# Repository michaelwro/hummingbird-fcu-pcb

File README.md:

# hummingbird-fcu-pcb

PCB files for the Hummingbird FCU quadcopter flight controller. Designed with KiCAD.

**Created By:** Michael Wrona, B.S. Aerospace Engineering

YouTube: [@MicWro Engr](https://www.youtube.com/channel/UCIeZzuXHGm7zqSFvT8xGoIQ)

Blog: [Michael Wrona's Blog](https://mwrona.com/)

**BEFORE USING, MAKE SURE YOU FULLY UNDERSTAND THE SCHEMATIC! USE AT YOUR OWN RISK! I AM NOT RESPONSIBLE FOR ANY DAMAGE TO YOUR ELECTRONICS!**

This is the place I store the KiCAD project files for the Humming Flight Control Unit, a quadcopter flight controller that I developed. Feel free to download it and print it!

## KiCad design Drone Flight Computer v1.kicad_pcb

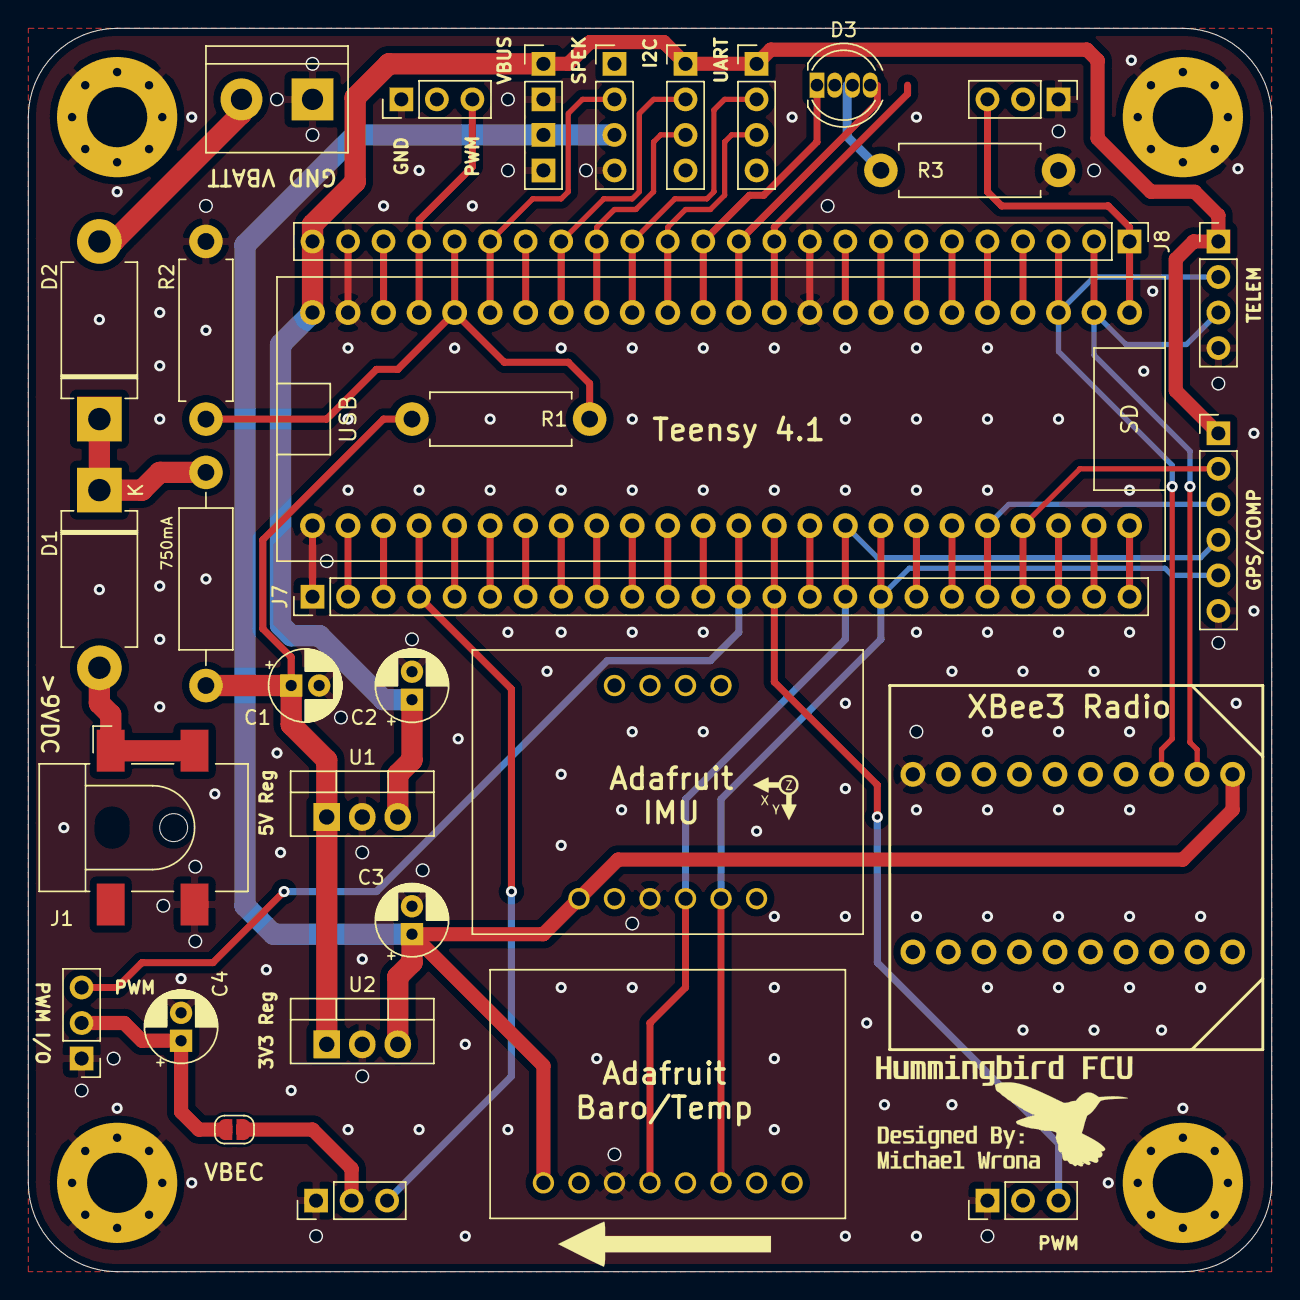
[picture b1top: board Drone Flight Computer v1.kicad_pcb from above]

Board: 2 copper layers, 88.9 x 88.9 mm, 37 parts (0 on the bottom side), 54 nets.

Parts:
C1, C2, C3: 100uF; CP_Radial_D5.0mm_P2.00mm
C4: 10uF; CP_Radial_D5.0mm_P2.00mm
D1, D2: Schottky; D_DO-201AD_P12.70mm_Horizontal
D3: LED_RGBC; LED_D5.0mm-4_RGB
F1: 750mA-1A; R_Axial_DIN0411_L9.9mm_D3.6mm_P15.24mm_Horizontal
H1, H2, H3, H4: MountingHole_Pad; MountingHole_4.3mm_M4_Pad_Via
J1: Jack; BarrelJack_CLIFF_FC681465S_SMT_Horizontal
J2: BATT_VCC; TerminalBlock_bornier-2_P5.08mm
J3: VOLT BUSES; PinHeader_1x04_P2.54mm_Vertical
J4: SPEK_RECV; PinHeader_1x04_P2.54mm_Vertical
J5: I2C1; PinHeader_1x04_P2.54mm_Vertical
J6, J9: UART1; PinHeader_1x04_P2.54mm_Vertical
J7: Pins Left; PinHeader_1x24_P2.54mm_Vertical
J8: Pins Right; PinHeader_1x24_P2.54mm_Vertical
J10: GPS_MAG; PinHeader_1x06_P2.54mm_Vertical
J11: M1_OUT; PinHeader_1x03_P2.54mm_Vertical
J12: M2_OUT; PinHeader_1x03_P2.54mm_Vertical
J13: M3_OUT; PinHeader_1x03_P2.54mm_Vertical
J14: M4_OUT; PinHeader_1x03_P2.54mm_Vertical
J15: PWM0_OUT; PinHeader_1x03_P2.54mm_Vertical
JP1: Sol_Jmp; SolderJumper-2_P1.3mm_Open_RoundedPad1.0x1.5mm
R1: 5k1; R_Axial_DIN0411_L9.9mm_D3.6mm_P12.70mm_Horizontal
R2: 1k; R_Axial_DIN0411_L9.9mm_D3.6mm_P12.70mm_Horizontal
R3: 330; R_Axial_DIN0411_L9.9mm_D3.6mm_P12.70mm_Horizontal
U1: UA78M05 5V LinReg; TO-220-3_Vertical
U2: UA78M33 3V3 LinReg; TO-220-3_Vertical
U3: Teensy4.1
U4: Adafruit_FXOS8700_FXAS21002_IMU
U5: XBee3_Breadboard_Breakout; XBee-3-breakout
U6: Adafruit_BMP388; Adafruit_BMP_388

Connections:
5V_BEC: J13.2, JP1.2
+3V3: C3.1, J3.3, J4.3, U2.2, U4.1, U5.1, U6.1
+5V: C2.1, J3.1, J5.1, J6.1, J8.24, J9.1, J10.1, U1.2, U3.48
GND: C1.2, C2.2, C3.2, C4.2, H1.1, H2.1, H3.1, H4.1, J1.2, J2.1, J3.2, J3.4, J4.4, J5.4, J6.4, J7.1, J8.10, J8.23, J9.4, J10.6, J11.1, J12.1, J13.1, J14.1, J15.1, R2.2, R3.1, U1.1, U2.1, U3.1, U3.34, U3.47, U4.3, U5.10, U6.3
I2C1_SCL: J5.2, J8.17, U3.41
I2C1_SDA: J5.3, J8.16, U3.40
I2C_SENS_SCL: J7.16, J10.4, U3.16, U4.4, U6.4
I2C_SENS_SDA: J7.17, J10.5, U3.17, U4.5, U6.6
LED_STATB: D3.3, J8.11, U3.35
LED_STATG: D3.2, J8.12, U3.36
LED_STATR: D3.1, J8.13, U3.37
unnamed: C4.1, J15.2, JP1.1
unnamed: D1.1, D2.1, F1.1
unnamed: D1.2, J1.1
unnamed: D2.2, J2.2
unnamed: D3.4, R3.2
unnamed: J7.2, U3.2
unnamed: J7.3, U3.3
unnamed: J7.5, U3.5
unnamed: J7.6, U3.6
unnamed: J7.7, U3.7
unnamed: J7.8, U3.8
unnamed: J7.9, U3.9
unnamed: J7.10, U3.10
unnamed: J7.11, U3.11
unnamed: J7.12, U3.12
unnamed: J7.15, U3.15
unnamed: J7.18, U3.18
unnamed: J7.19, U3.19
unnamed: J7.22, U3.22
unnamed: J7.23, U3.23
unnamed: J7.24, U3.24
unnamed: J8.4, U3.28
unnamed: J8.5, U3.29
unnamed: J8.6, U3.30
unnamed: J8.7, U3.31
unnamed: J8.8, U3.32
unnamed: J8.9, U3.33
unnamed: J8.18, U3.42
unnamed: J8.22, U3.46
PWM0_IO: J7.13, J15.3, U3.13
PWM_M1: J8.21, J11.3, U3.45
PWM_M2: J8.1, J12.3, U3.25
PWM_M3: J7.4, J13.3, U3.4
PWM_M4: J7.14, J14.3, U3.14
UART1_RX: J6.3, J8.14, U3.38
UART1_TX: J6.2, J8.15, U3.39
UART_GPS_RX: J7.20, J10.3, U3.20
UART_GPS_TX: J7.21, J10.2, U3.21
UART_SPEKREC_RX: J4.2, J8.19, U3.43
UART_TLM_RX: J8.2, J9.3, U3.26, U5.2
UART_TLM_TX: J8.3, J9.2, U3.27, U5.3
VCC: C1.1, F1.2, R1.1, U1.3, U2.3
VREAD_VCC: J8.20, R1.2, R2.1, U3.44

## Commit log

2021-03-13 Added pics to readme
2021-03-13 First pcb upload
2021-03-13 Moved to folder
2021-03-13 rm old files
